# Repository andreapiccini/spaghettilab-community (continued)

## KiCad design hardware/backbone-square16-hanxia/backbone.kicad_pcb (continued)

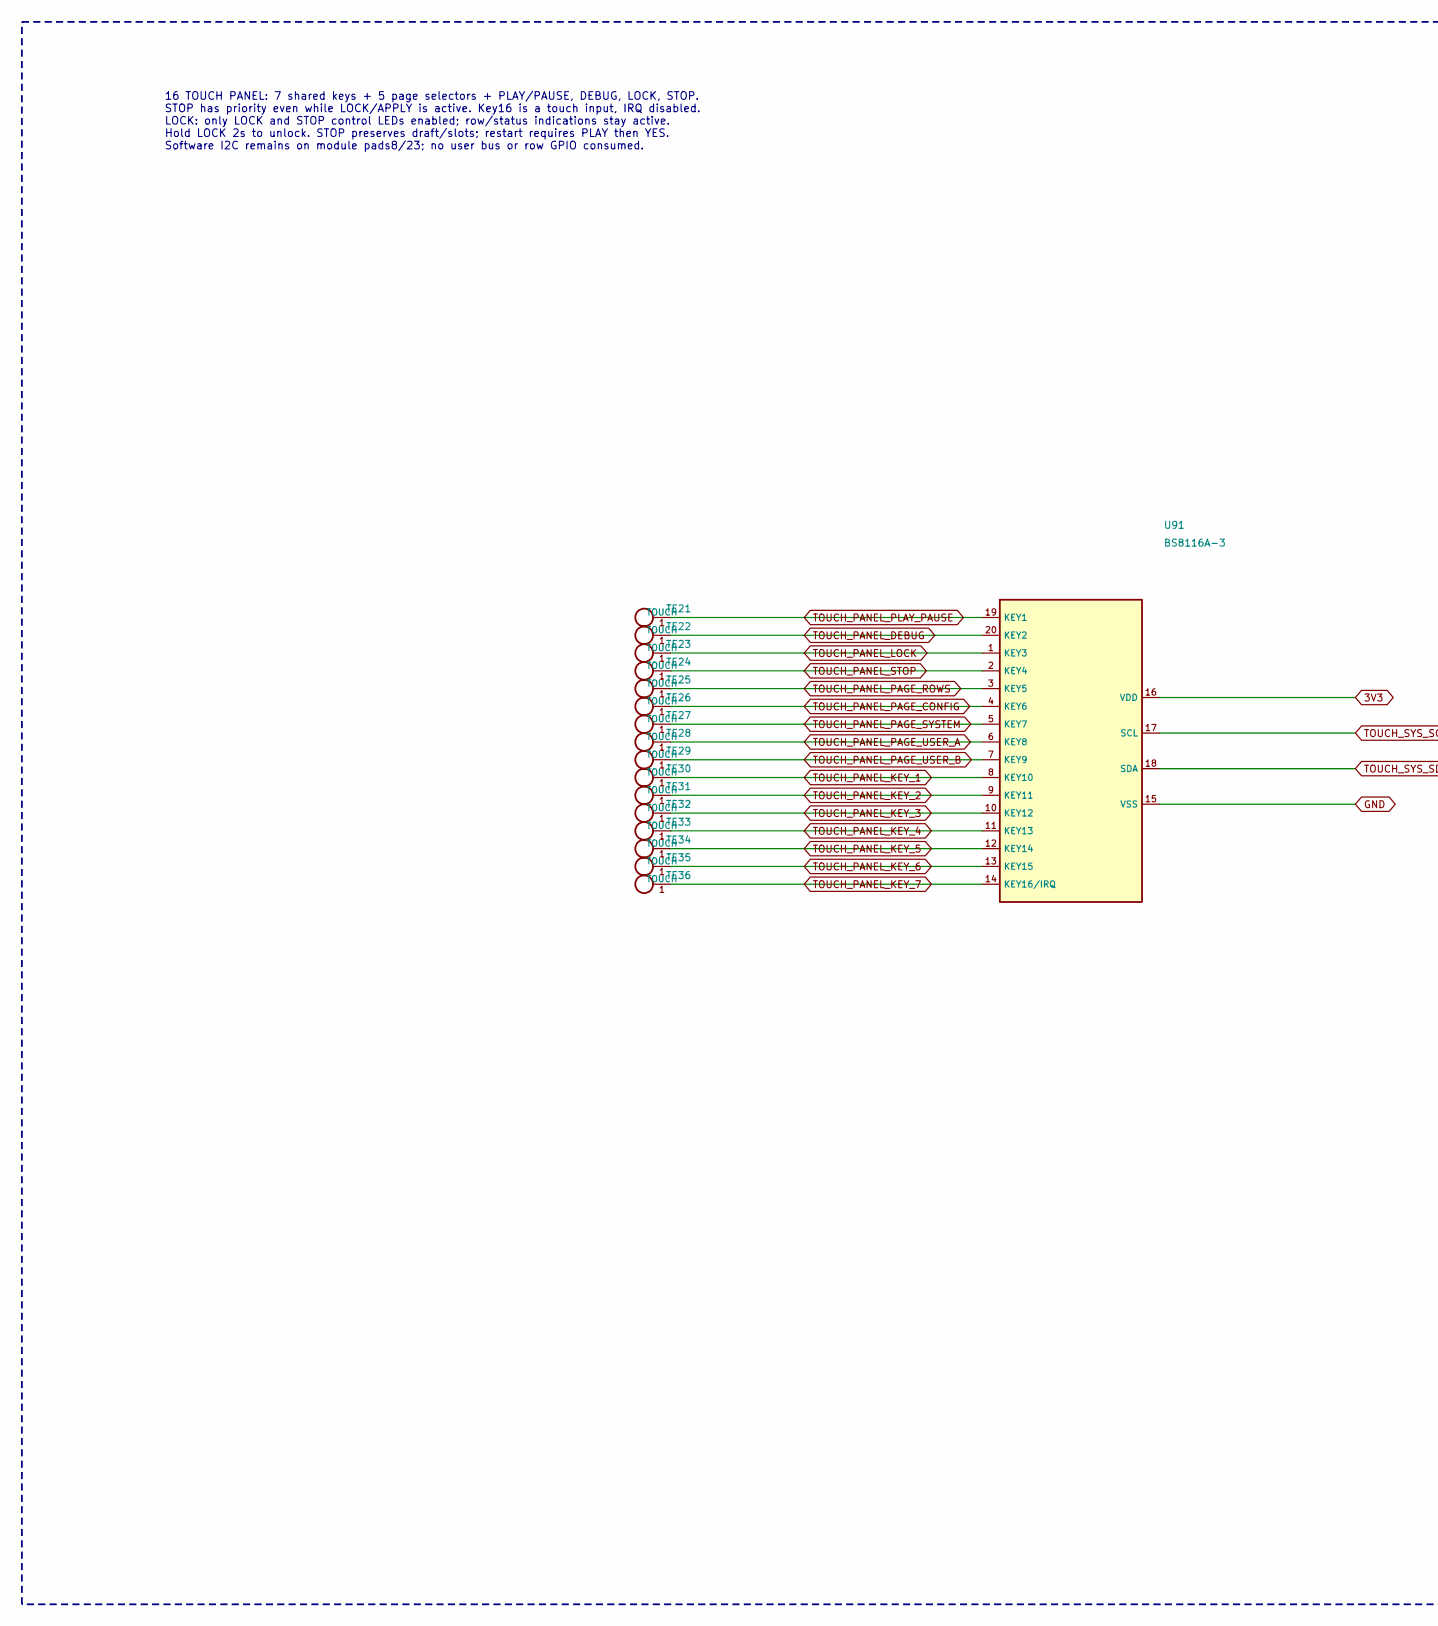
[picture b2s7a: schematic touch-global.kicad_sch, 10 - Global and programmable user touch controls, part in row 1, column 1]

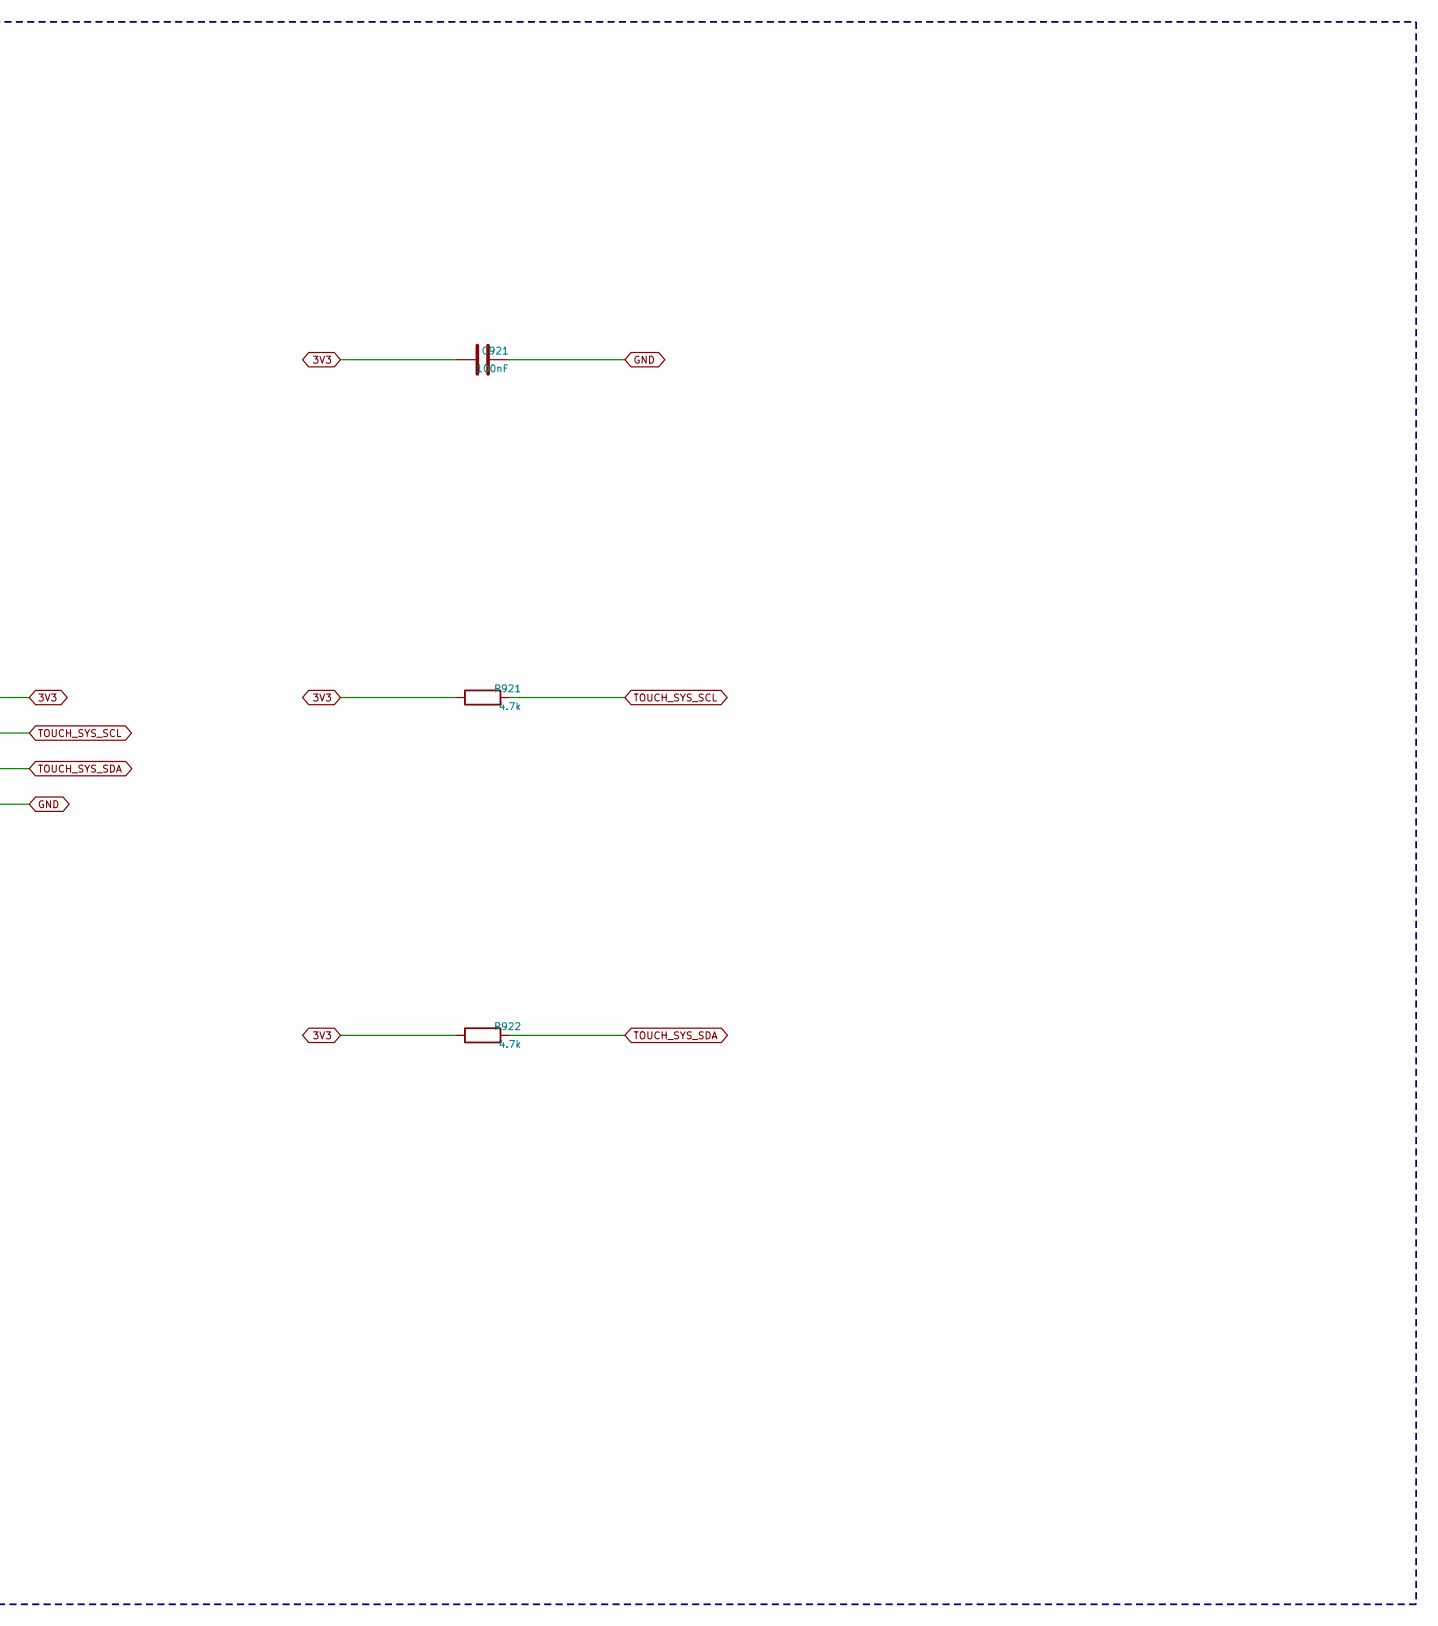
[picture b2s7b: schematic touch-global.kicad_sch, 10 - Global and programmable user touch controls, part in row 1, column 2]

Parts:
C921: 100nF; C_0603_1608Metric
R921, R922: 4.7k; R_0603_1608Metric; MPN 0603WAF4701T5E; LCSC Part C23162
TE21: PLAY_PAUSE; PanelTouch_PLAY_PAUSE
TE22: DEBUG; PanelTouch_DEBUG
TE23: LOCK; PanelTouch_LOCK
TE24: STOP; PanelTouch_STOP
TE25: PAGE_ROWS; PanelTouch_PAGE_ROWS
TE26: PAGE_CONFIG; PanelTouch_PAGE_CONFIG
TE27: PAGE_SYSTEM; PanelTouch_PAGE_SYSTEM
TE28: PAGE_USER_A; PanelTouch_PAGE_USER_A
TE29: PAGE_USER_B; PanelTouch_PAGE_USER_B
TE30: KEY_1; PanelTouch_KEY_1
TE31: KEY_2; PanelTouch_KEY_2
TE32: KEY_3; PanelTouch_KEY_3
TE33: KEY_4; PanelTouch_KEY_4
TE34: KEY_5; PanelTouch_KEY_5
TE35: KEY_6; PanelTouch_KEY_6
TE36: KEY_7; PanelTouch_KEY_7
U91: BS8116A-3; SSOP-20_3.9x8.7mm_P0.635mm

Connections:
3V3: C921.1, R921.1, R922.1, U91.16 (VDD); also elsewhere on the board
GND: C921.2, U91.15 (VSS); also elsewhere on the board
TOUCH_PANEL_DEBUG: TE22.1, U91.20 (KEY2)
TOUCH_PANEL_KEY_1: TE30.1, U91.8 (KEY10)
TOUCH_PANEL_KEY_2: TE31.1, U91.9 (KEY11)
TOUCH_PANEL_KEY_3: TE32.1, U91.10 (KEY12)
TOUCH_PANEL_KEY_4: TE33.1, U91.11 (KEY13)
TOUCH_PANEL_KEY_5: TE34.1, U91.12 (KEY14)
TOUCH_PANEL_KEY_6: TE35.1, U91.13 (KEY15)
TOUCH_PANEL_KEY_7: TE36.1, U91.14 (KEY16/IRQ)
TOUCH_PANEL_LOCK: TE23.1, U91.1 (KEY3)
TOUCH_PANEL_PAGE_CONFIG: TE26.1, U91.4 (KEY6)
TOUCH_PANEL_PAGE_ROWS: TE25.1, U91.3 (KEY5)
TOUCH_PANEL_PAGE_SYSTEM: TE27.1, U91.5 (KEY7)
TOUCH_PANEL_PAGE_USER_A: TE28.1, U91.6 (KEY8)
TOUCH_PANEL_PAGE_USER_B: TE29.1, U91.7 (KEY9)
TOUCH_PANEL_PLAY_PAUSE: TE21.1, U91.19 (KEY1)
TOUCH_PANEL_STOP: TE24.1, U91.2 (KEY4)
TOUCH_SYS_SCL: R921.2, U91.17 (SCL); also elsewhere on the board
TOUCH_SYS_SDA: R922.2, U91.18 (SDA); also elsewhere on the board

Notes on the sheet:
16 TOUCH PANEL: 7 shared keys + 5 page selectors + PLAY/PAUSE, DEBUG, LOCK, STOP. STOP has priority even while LOCK/APPLY is active. Key16 is a touch input, IRQ disabled. LOCK: only LOCK and STOP control LEDs enabled; row/status indications stay active. Hold LOCK 2s to unlock. STOP preserves draft/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

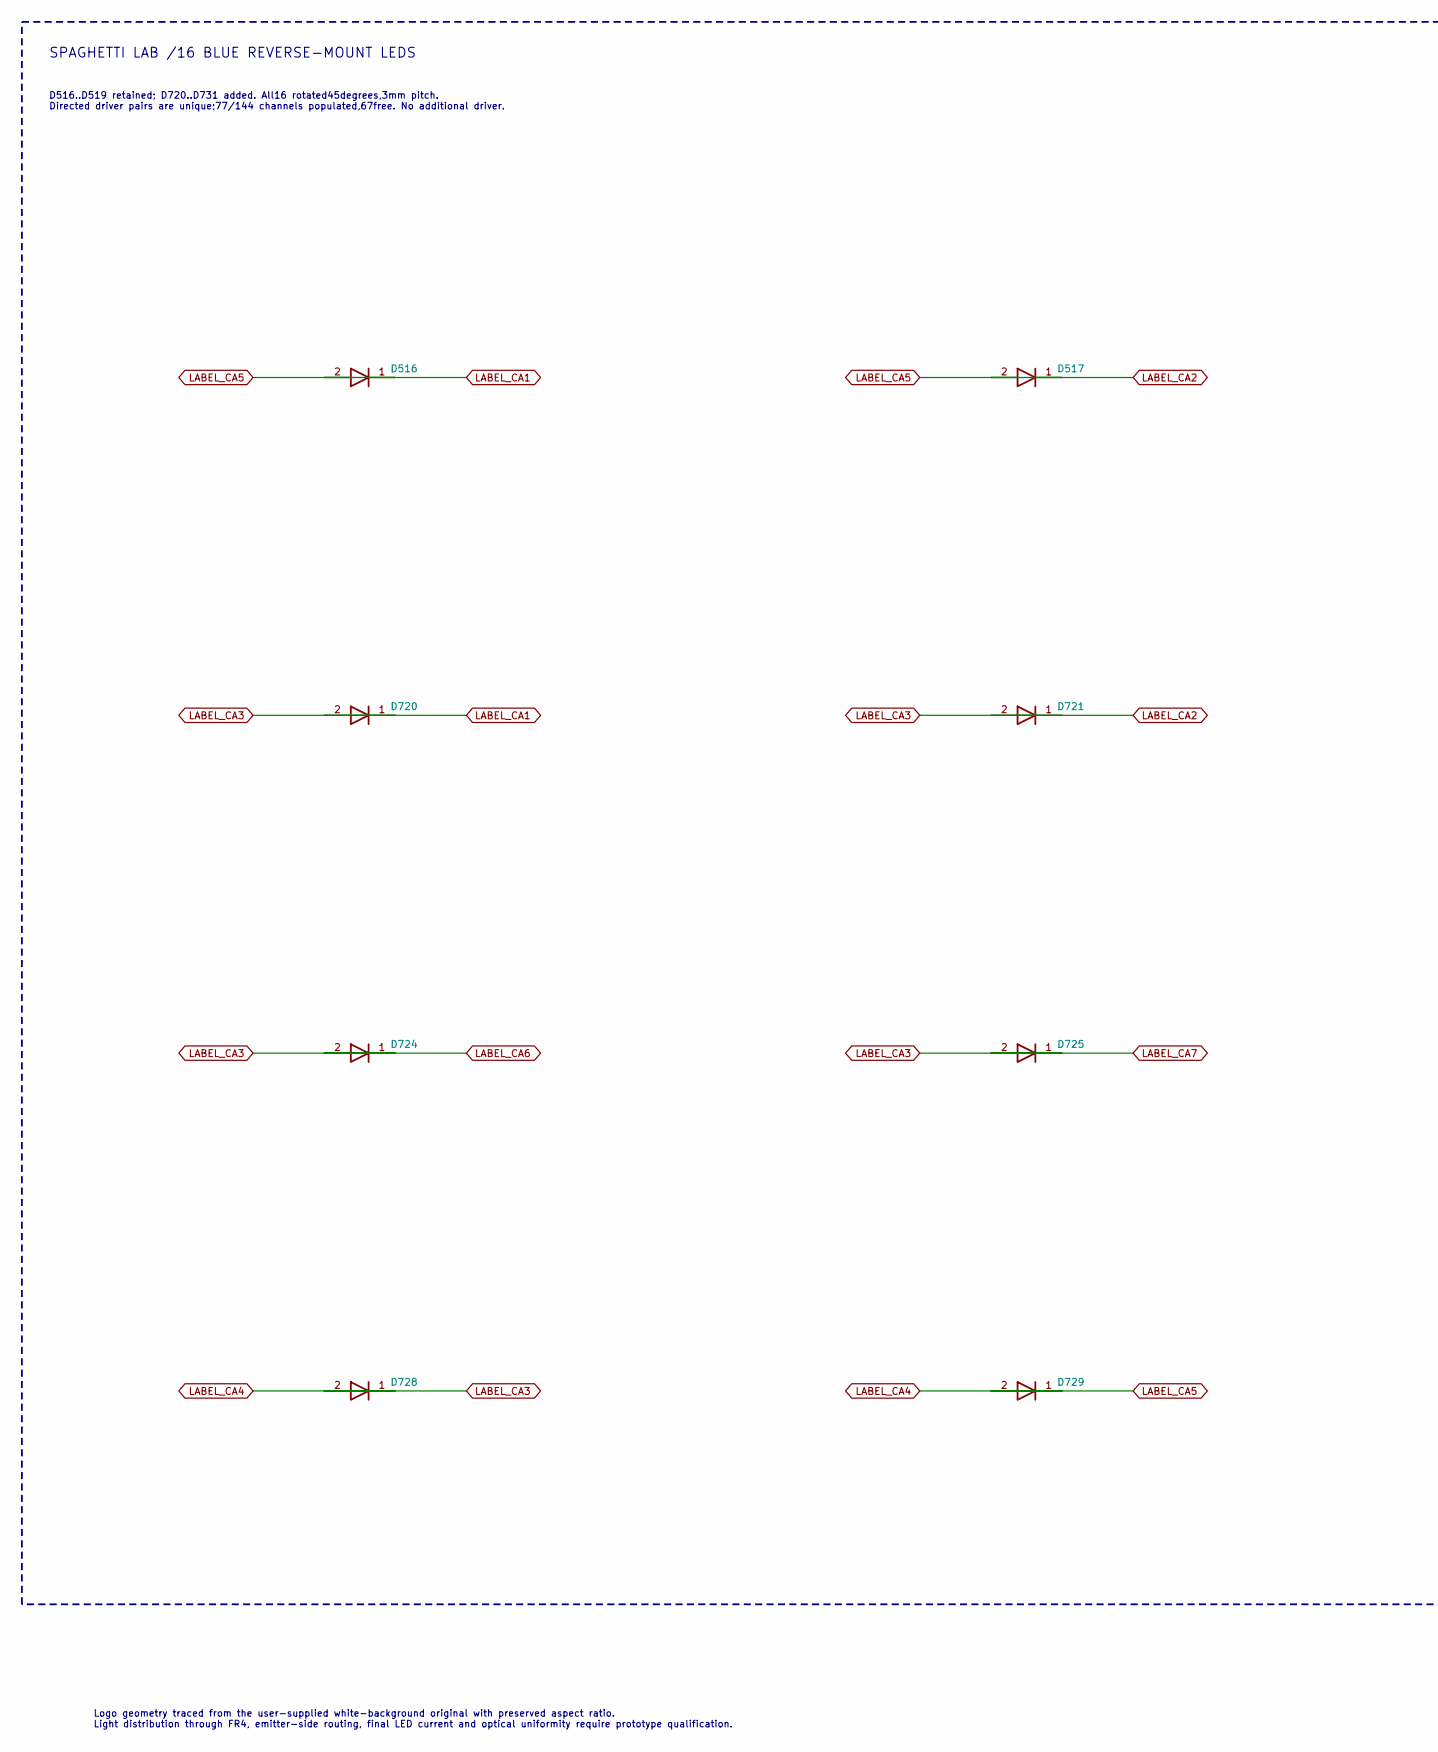
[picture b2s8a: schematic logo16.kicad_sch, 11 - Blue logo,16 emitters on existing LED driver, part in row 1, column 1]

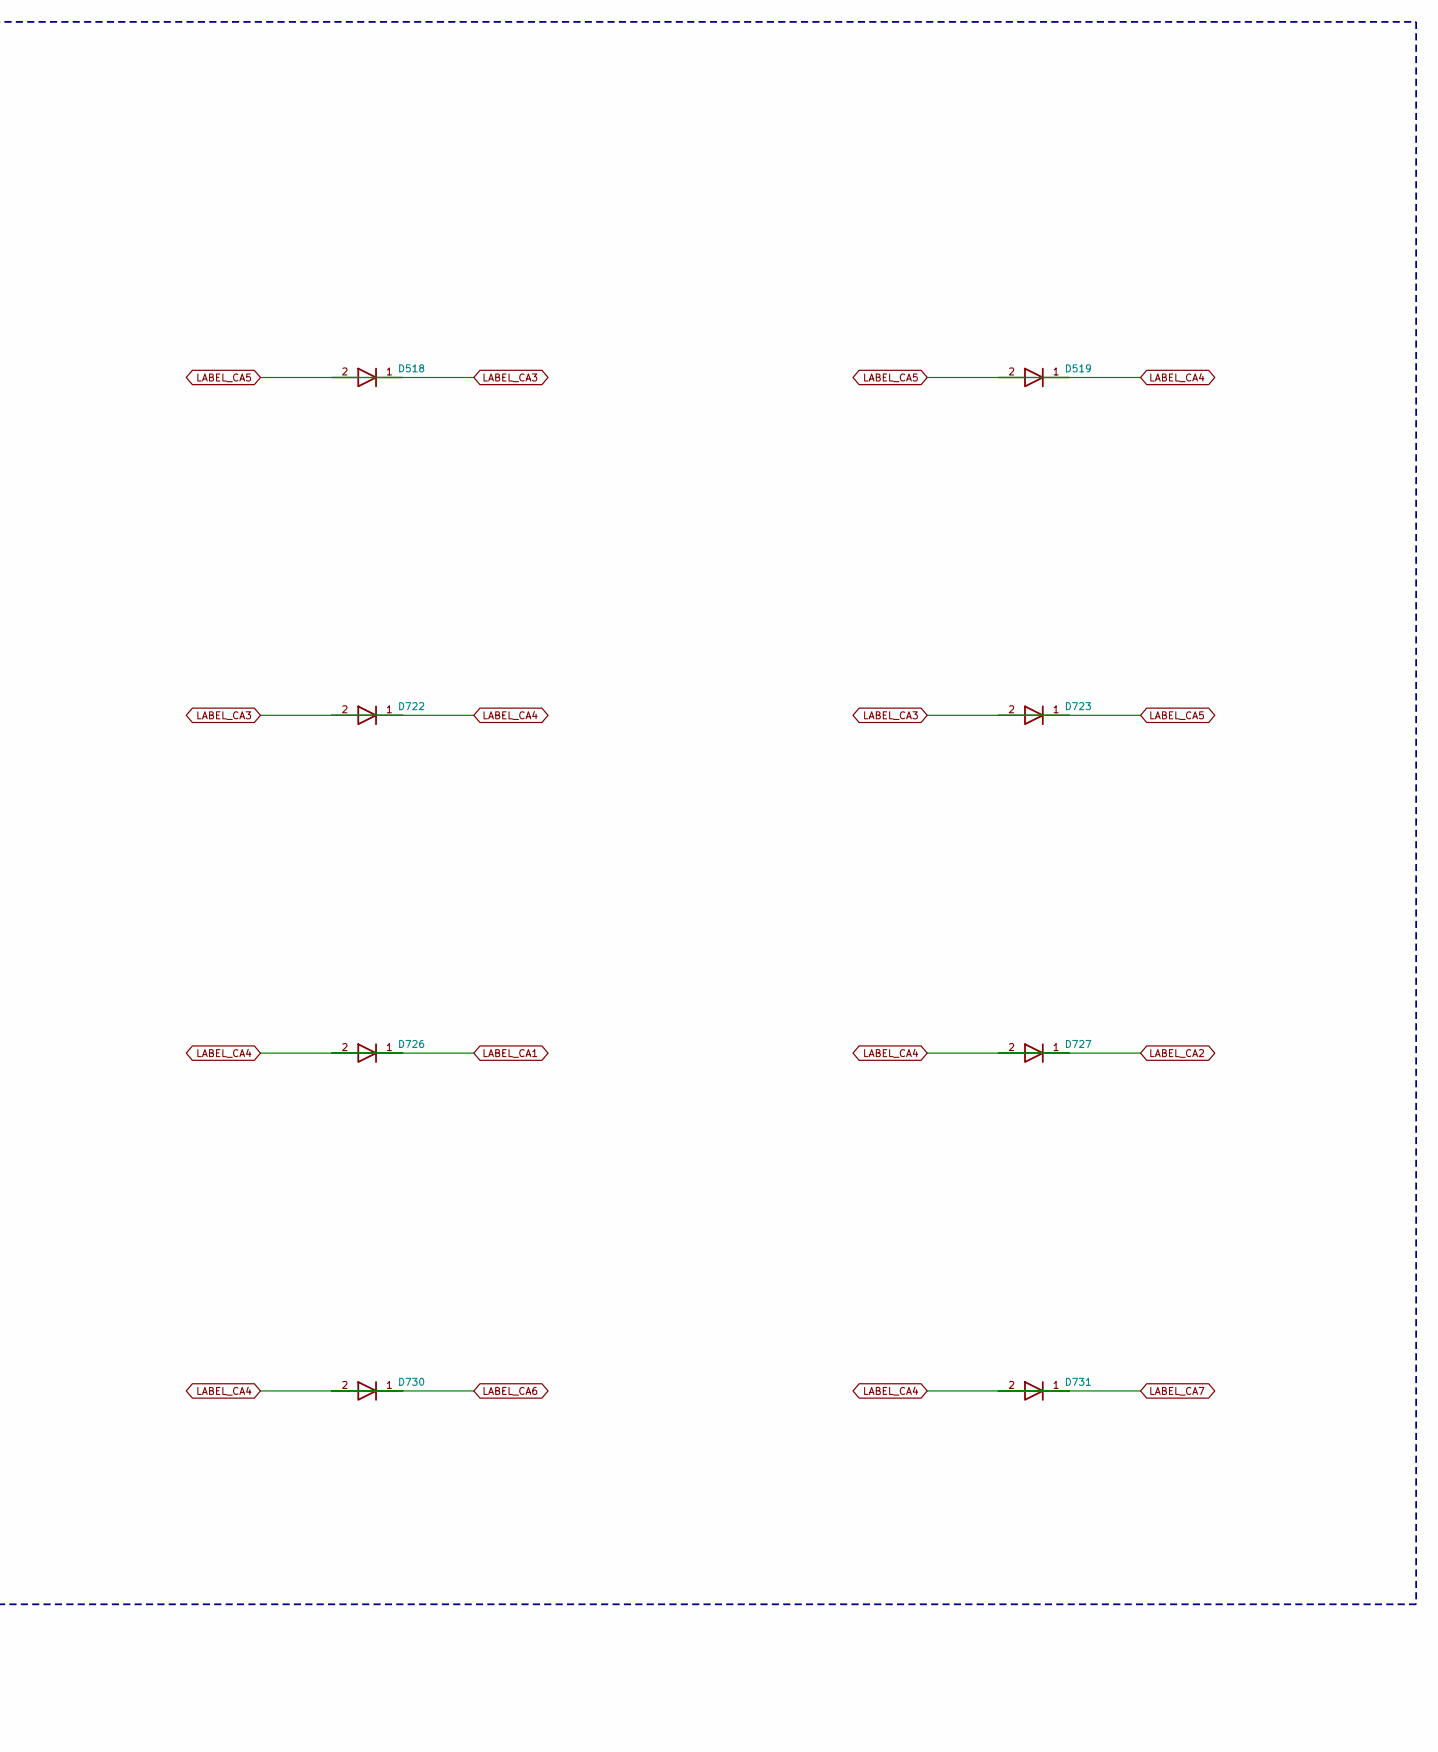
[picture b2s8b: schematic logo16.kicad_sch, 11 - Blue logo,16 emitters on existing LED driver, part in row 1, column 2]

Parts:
D516, D517, D518, D519, D720, D721, D722, D723, D724, D725, D726, D727, D728, D729, D730, D731: XL-3216UBC-FB; XINGLIGHT_XL3216_Reverse_Word_Window; MPN XL-3216UBC-FB; LCSC Part C3646941

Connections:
LABEL_CA1: D516.2 (A), D720.2 (A), D726.2 (A); also elsewhere on the board
LABEL_CA2: D517.2 (A), D721.2 (A), D727.2 (A); also elsewhere on the board
LABEL_CA3: D518.2 (A), D720.1 (K), D721.1 (K), D722.1 (K), D723.1 (K), D724.1 (K), D725.1 (K), D728.2 (A); also elsewhere on the board
LABEL_CA4: D519.2 (A), D722.2 (A), D726.1 (K), D727.1 (K), D728.1 (K), D729.1 (K), D730.1 (K), D731.1 (K); also elsewhere on the board
LABEL_CA5: D516.1 (K), D517.1 (K), D518.1 (K), D519.1 (K), D723.2 (A), D729.2 (A); also elsewhere on the board
LABEL_CA6: D724.2 (A), D730.2 (A); also elsewhere on the board
LABEL_CA7: D725.2 (A), D731.2 (A); also elsewhere on the board

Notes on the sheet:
SPAGHETTI LAB /16 BLUE REVERSE-MOUNT LEDS
D516..D519 retained; D720..D731 added. All16 rotated45degrees,3mm pitch. Directed driver pairs are unique;77/144 channels populated,67free. No additional driver.
Logo geometry traced from the user-supplied white-background original with preserved aspect ratio. Light distribution through FR4, emitter-side routing, final LED current and optical uniformity require prototype qualification.

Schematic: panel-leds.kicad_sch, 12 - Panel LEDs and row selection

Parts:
D800, D801, D802, D803, D804, D805, D806, D807, D808, D809, D810, D811, D812, D813, D814, D815, D816, D817, D818, D819, D820, D821, D822, D823, D824, D825, D826, D827, D828, D829, D830, D831, D832, D833, D834, D835, D836, D837, D838, D839, D840, D841, D842, D843, D844, D845, D846, D847, D848, D849, D850, D851: XL-3216UGC-FB; XINGLIGHT_XL3216_Reverse_Word_Window; LCSC Part C3646937

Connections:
LABEL_CA1: D805.2 (A), D814.2 (A), D822.2 (A); also elsewhere on the board
LABEL_CA2: D806.2 (A), D815.2 (A), D823.2 (A); also elsewhere on the board
LABEL_CA3: D807.2 (A), D811.2 (A), D816.2 (A), D824.2 (A); also elsewhere on the board
LABEL_CA4: D800.1 (K), D801.1 (K), D808.2 (A), D817.2 (A), D825.2 (A); also elsewhere on the board
LABEL_CA5: D802.1 (K), D803.1 (K), D804.1 (K), D809.2 (A), D818.2 (A), D826.2 (A); also elsewhere on the board
LABEL_CA6: D802.2 (A), D805.1 (K), D806.1 (K), D807.1 (K), D808.1 (K), D809.1 (K), D810.1 (K), D819.2 (A), D827.2 (A); also elsewhere on the board
LABEL_CA7: D803.2 (A), D810.2 (A), D811.1 (K), D812.1 (K), D813.1 (K), D820.2 (A), D828.2 (A); also elsewhere on the board
LABEL_CA8: D800.2 (A), D812.2 (A), D814.1 (K), D815.1 (K), D816.1 (K), D817.1 (K), D818.1 (K), D819.1 (K), D820.1 (K), D821.1 (K), D829.2 (A); also elsewhere on the board
LABEL_CA9: D801.2 (A), D804.2 (A), D813.2 (A), D821.2 (A), D822.1 (K), D823.1 (K), D824.1 (K), D825.1 (K), D826.1 (K), D827.1 (K), D828.1 (K), D829.1 (K); also elsewhere on the board
LABEL_CB1: D830.2 (A), D837.2 (A), D845.2 (A); also elsewhere on the board
LABEL_CB2: D831.2 (A), D838.2 (A), D846.2 (A); also elsewhere on the board
LABEL_CB3: D832.2 (A), D839.2 (A), D847.2 (A); also elsewhere on the board
LABEL_CB4: D840.2 (A), D848.2 (A); also elsewhere on the board
LABEL_CB5: D830.1 (K), D831.1 (K), D832.1 (K), D833.1 (K), D834.1 (K), D835.1 (K), D836.1 (K), D841.2 (A), D849.2 (A); also elsewhere on the board
LABEL_CB6: D833.2 (A), D837.1 (K), D838.1 (K), D839.1 (K), D840.1 (K), D841.1 (K), D842.1 (K), D843.1 (K), D844.1 (K), D850.2 (A); also elsewhere on the board
LABEL_CB7: D834.2 (A), D842.2 (A), D845.1 (K), D846.1 (K), D847.1 (K), D848.1 (K), D849.1 (K), D850.1 (K), D851.1 (K); also elsewhere on the board
LABEL_CB8: D835.2 (A), D843.2 (A), D851.2 (A); also elsewhere on the board
LABEL_CB9: D836.2 (A), D844.2 (A); also elsewhere on the board

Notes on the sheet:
Independent PWM channels. LOCK masks all control LEDs except LOCK and STOP. Row selection/status remains visible. Optical windows require translucent overlay/light isolation.
KEY1_PAGE0
KEY1_PAGE1
KEY1_PAGE2
KEY1_PAGE3
KEY1_PAGE4
KEY2_PAGE0
KEY2_PAGE1
KEY2_PAGE2
KEY2_PAGE3
KEY2_PAGE4
KEY3_PAGE0
KEY3_PAGE1
KEY3_PAGE2
KEY3_PAGE3
KEY3_PAGE4
KEY4_PAGE0
KEY4_PAGE1
KEY4_PAGE2
KEY4_PAGE3
KEY4_PAGE4
KEY5_PAGE0
KEY5_PAGE1
KEY5_PAGE2
KEY5_PAGE3
KEY5_PAGE4
KEY6_PAGE0
KEY6_PAGE1
KEY6_PAGE2
KEY6_PAGE3
KEY6_PAGE4
KEY7_PAGE0
KEY7_PAGE1
KEY7_PAGE2
KEY7_PAGE3
KEY7_PAGE4
SELECT_A1
SELECT_A2
SELECT_A3
SELECT_A4

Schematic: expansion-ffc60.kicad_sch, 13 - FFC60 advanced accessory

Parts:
J32: FPC-05FB-60PH20; XUNPU_FPC-05FB-60PH20; LCSC Part C2856839

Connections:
3V3: J32.57; also elsewhere on the board
5V: J32.59, J32.60; also elsewhere on the board
EXP_RESET_N: J32.58; also elsewhere on the board
GND: J32.3, J32.6, J32.9, J32.12, J32.15, J32.18, J32.21, J32.24, J32.27, J32.30, J32.33, J32.36, J32.39, J32.42, J32.45, J32.48, J32.55, J32.56; also elsewhere on the board
GPIO1: J32.2; also elsewhere on the board
GPIO2: J32.26; also elsewhere on the board
GPIO3: J32.5; also elsewhere on the board
GPIO4: J32.14; also elsewhere on the board
GPIO6: J32.8; also elsewhere on the board
GPIO7: J32.11; also elsewhere on the board
GPIO8: J32.29; also elsewhere on the board
GPIO9: J32.32; also elsewhere on the board
GPIO10: J32.35; also elsewhere on the board
GPIO35: J32.17; also elsewhere on the board
GPIO36: J32.20; also elsewhere on the board
GPIO37: J32.23; also elsewhere on the board
GPIO38: J32.38; also elsewhere on the board
GPIO39: J32.41; also elsewhere on the board
GPIO40: J32.44; also elsewhere on the board
GPIO41: J32.47; also elsewhere on the board
GPIO43: J32.52; also elsewhere on the board
GPIO44: J32.51; also elsewhere on the board
I2C_USER_SCL: J32.54; also elsewhere on the board
I2C_USER_SDA: J32.53; also elsewhere on the board
ROW_L01: J32.1; also elsewhere on the board
ROW_L02: J32.4; also elsewhere on the board
ROW_L03: J32.7; also elsewhere on the board
ROW_L04: J32.10; also elsewhere on the board
ROW_L05: J32.13; also elsewhere on the board
ROW_L06: J32.16; also elsewhere on the board
ROW_L07: J32.19; also elsewhere on the board
ROW_L08: J32.22; also elsewhere on the board
ROW_R01: J32.25; also elsewhere on the board
ROW_R02: J32.28; also elsewhere on the board
ROW_R03: J32.31; also elsewhere on the board
ROW_R04: J32.34; also elsewhere on the board
ROW_R05: J32.37; also elsewhere on the board
ROW_R06: J32.40; also elsewhere on the board
ROW_R07: J32.43; also elsewhere on the board
ROW_R08: J32.46; also elsewhere on the board

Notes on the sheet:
FFC60 ADVANCED ACCESSORY - component side, cable through rounded slot 1..48: ROW / GPIO / GND triplets. Do not bridge ROW to GPIO on an accessory. 49..52: auxiliary GPIO aliases (UART0 may emit boot logs); 53/54: user I2C. 55/56 GND; 57 3V3; 58 EXP_RESET_N (LOW = outputs must be disabled); 59/60 5V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

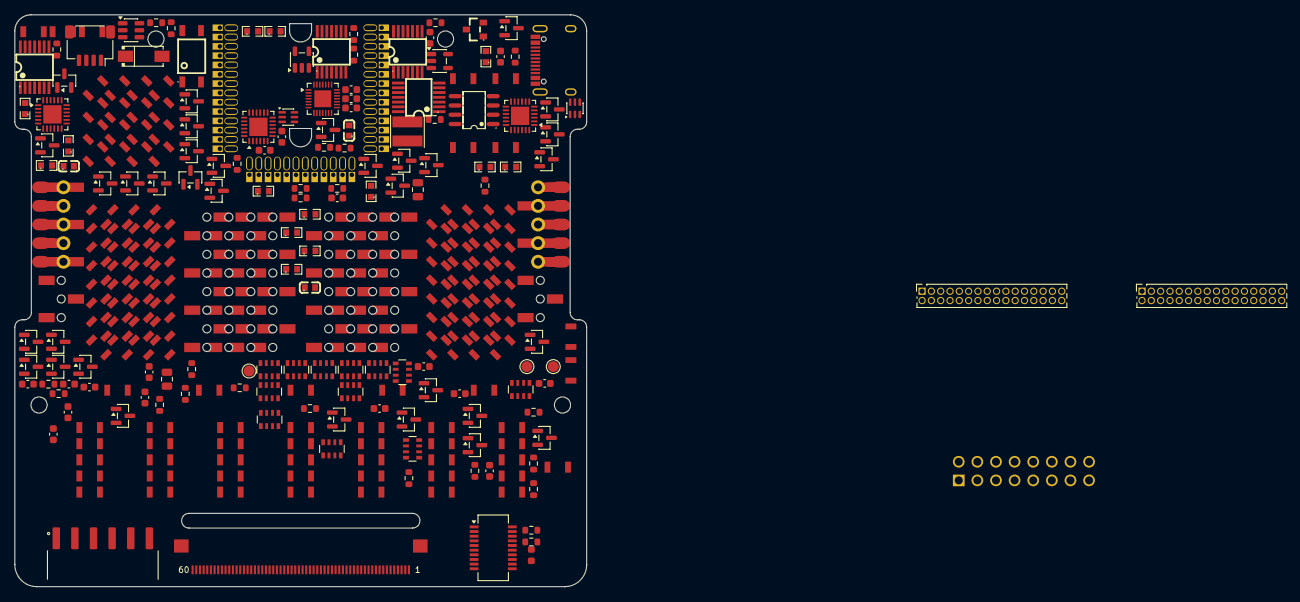
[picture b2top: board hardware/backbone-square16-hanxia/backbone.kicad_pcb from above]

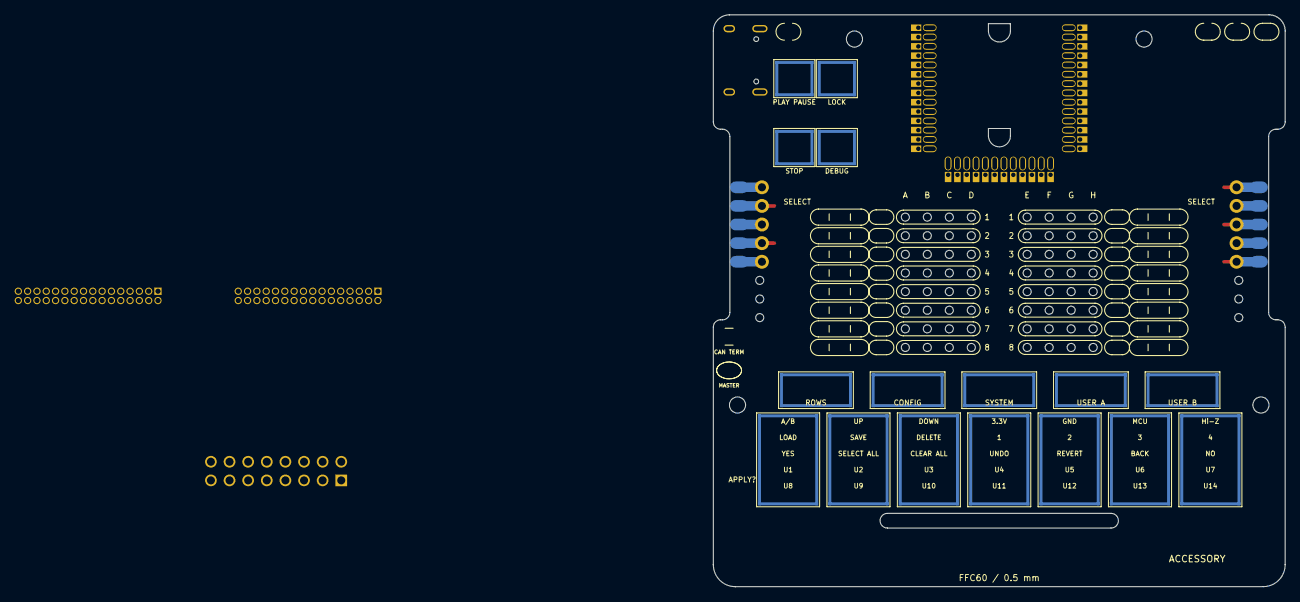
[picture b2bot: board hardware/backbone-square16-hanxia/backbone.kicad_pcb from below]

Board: 4 copper layers, 78.0 x 78.0 mm, 306 parts (17 on the bottom side), 167 nets.

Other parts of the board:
H1, H2, H3, H4: MountingHole; MountingHole_2.2mm_M2_DIN965

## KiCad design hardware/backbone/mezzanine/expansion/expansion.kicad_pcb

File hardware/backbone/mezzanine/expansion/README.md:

# Expansion

Removable AG32 instrumentation module for the SpaghettiLAB backbone.

Open `expansion.kicad_pro`, `expansion.kicad_sch` or `expansion.kicad_pcb`. Carrier: `../../backbone.kicad_pcb`.

PCB components are placed; routing and physical qualification remain open. See [layout and limits](../../MEZZANINE-LAYOUT.md) and [current electrical interface](../../CURRENT-REVISION.md).

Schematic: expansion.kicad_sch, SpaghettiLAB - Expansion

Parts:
C90, C91, C92, C93, C94, C95, C96, C97, C98, C100, C101, C121, C122, C123, C131: 100nF; C_0603_1608Metric; LCSC C14663
C99: 1uF; C_0603_1608Metric; LCSC C15849
J5: FH12-24S-0.5SH(55); Hirose_FH12-24S-0.5SH_1x24-1MP_P0.50mm_Horizontal; LCSC C202112
J10, J11: 61083-061402LF; CONN-SMD_61083-061402LF; LCSC C464610
J12: ESP_AUX_24; PinHeader_2x12_P2.54mm_Vertical_SMD
R70, R72, R73, R79, R80, R83, R84, R109: 10k; R_0603_1608Metric; LCSC C25804
R71, R74, R75, R76, R78, R110, R111: 100k; R_0603_1608Metric; LCSC C25803
R77: 4.7k 0.1% 25ppm; R_0603_1608Metric; LCSC C513565
R81, R82: 22R; R_0603_1608Metric; LCSC C23345
R85, R86, R87, R88: 1k; R_0603_1608Metric; LCSC C21190
R107: 10k; R_0603_1608Metric; MPN 0603WAF1002T5E; LCSC C25804
R108: 100k; R_0603_1608Metric; MPN 0603WAF1003T5E; LCSC C25803
R116: 0R; R_0603_1608Metric; LCSC C21189
TP18, TP19, TP21: SMD/0.6mm; TestPoint_Pad_D1.0mm
TP22: AG_NRST; TestPoint_Pad_D1.0mm
TP23: AG_JTMS; TestPoint_Pad_D1.0mm
TP24: AG_JTCK; TestPoint_Pad_D1.0mm
TP25: AG_JTDI; TestPoint_Pad_D1.0mm
TP26: AG_JTDO; TestPoint_Pad_D1.0mm
TP27: AG_JNTRST; TestPoint_Pad_D1.0mm
TP41: DAC1_SPARE; TestPoint_Pad_D1.0mm
TP42: SPARE_IO_17; TestPoint_Pad_D1.0mm
TP43: SPARE_IO_33; TestPoint_Pad_D1.0mm
TP44: SPARE_IO_34; TestPoint_Pad_D1.0mm
TP45: ISO4_CTRL; TestPoint_Pad_D1.0mm
TP46: ISO5_CTRL; TestPoint_Pad_D1.0mm
TP47: AG_UART_RX; TestPoint_Pad_D1.0mm
TP48: AG_UART_TX; TestPoint_Pad_D1.0mm
TP49: AG_BOOT0; TestPoint_Pad_D1.0mm
U14: AG32VF407VGT6; LQFP-100_L14.0-W14.0-P0.50-LS16.0-TL; LCSC C5336269
U16: INA226AIDGSR; MSOP-10_L3.0-W3.0-P0.50-LS5.0-BL; LCSC C49851
U17, U18, U19: 74HC4051BQ,115; DHVQFN-16_L3.5-W2.5-P0.50-BL-EP; LCSC C128429
U32: DAC_R77_BYPASS; SOT-363_SC-70-6; LCSC C38663
X1: 20MHz; OSC-SMD_4P-L3.2-W2.5-BL; LCSC C390499

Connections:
5V: J10.1, J10.2, J11.1, J11.2, J12.22
/AG_BOOT0: R83.2, R87.2, TP49.1, U14.94 (BOOT0)
/AG_BOOT1: R84.2, U14.37 (BOOT1)
/AG_JNTRST_N: R73.2, TP27.1 (1_1), U14.90 (JNTRST_N)
/AG_JTCK: TP24.1 (1_1), U14.76 (JTCK)
/AG_JTDI: TP25.1 (1_1), U14.77 (JTDI)
/AG_JTDO: TP26.1 (1_1), U14.89 (JTDO)
/AG_JTMS: TP23.1 (1_1), U14.72 (JTMS)
/AG_NRST_N: C92.1, R72.2, R88.2, TP22.1 (1_1), U14.14 (NRST_N)
/CLK20M: U14.12 (OSC_IN), U14.18 (CLK20M_FPGA), X1.3 (OUT)
/DAC1_SPARE: J5.22, TP41.1 (1_1), U14.30 (DAC1_SPARE)
/DAC_INHIBIT: R71.2, U14.81 (DAC_INHIBIT), U19.6 (E_INHIBIT)
/DAC_S0: U14.78 (DAC_S0), U19.11 (S0)
/DAC_S1: U14.79 (DAC_S1), U19.10 (S1)
/DAC_S2: U14.80 (DAC_S2), U19.9 (S2)
/INA_ALERT_N: R76.2, U14.84 (INA_ALERT_N), U16.3 (Alert)
/SHUNT_HIGH_SELECTED: U16.10 (VIN+), U17.3 (Z)
/SHUNT_LOW_SELECTED: U16.8 (VBUS), U16.9 (VIN-), U18.3 (Z)
/SPARE_IO_17: TP42.1 (1_1), U14.17 (ADC_IN12_SPARE)
/SPARE_IO_33: TP43.1 (1_1), U14.33 (ADC_IN14_SPARE)
/SPARE_IO_34: TP44.1 (1_1), U14.34 (ADC_IN15_SPARE)
/USB_AG_D+: R82.1, U14.71 (USB_DP)
/USB_AG_D-: R81.1, U14.70 (USB_DM)
A0: J10.6, J12.6, U14.38 (ESP_A0)
A1: J10.9, J12.7, U14.39 (ESP_A1)
A2: J10.13, J12.8, U14.40 (ESP_A2)
A3: J10.17, J12.9, U14.41 (ESP_A3)
A4: J10.21, J12.10, U14.42 (ESP_A4)
A5: J10.24, J12.11, U14.43 (ESP_A5)
AG_BOOT_UART_RX: R85.2, TP47.1, U14.69 (ISO5_N)
AG_BOOT_UART_TX: R86.1, TP48.1, U14.68 (ISO4_N)
AG_CAN_TX: J10.34, U14.92 (CAN_TX)
AG_ISO4_N: J10.36, U14.35 (ADC_IN8_SPARE)
AG_ISO5_N: J10.37, U14.36 (ADC_IN9_SPARE)
AG_LED_DATA: J10.38, U14.7 (LED_DATA)
BOOT: J10.28, J12.1, U14.61 (N_GATE4)
CAN_H: J11.46
CAN_L: J11.47
CAN_RX: J5.8, J10.39, U14.93 (CAN_RX)
CTRL13: J10.41, J12.12, R74.2, U14.86 (SPI_CS_N)
CTRL14: J5.19, J10.42, U14.87 (SPI_SCLK)
DAC_BYPASS_N: R78.2, U14.85 (DAC_BYPASS_N), U32.6 (S_AG_READY)
DAC_LIMITED: R77.2, U14.16 (ADC_LIMIT/IN11), U19.3 (Z), U32.4 (A_OUT)
DAC_RAW: R77.1, U14.15 (ADC_RAW/IN10), U14.29 (DAC0_OUT), U32.3 (B1_ESP)
ESP35_AUX: J10.43, J12.13, U14.64 (ISO0_N)
ESP36_AUX: J10.44, J12.14, U14.65 (ISO1_N)
ESP37_AUX: J10.46, J12.15, U14.66 (ISO2_N)
ESP_AG_BOOT0: J10.29, J12.2, R87.1, U14.67 (ISO3_N)
ESP_AG_RESET_N: J10.31, J12.3, R88.1, U14.82 (INA_SDA)
ESP_CAN_TX: J5.7, J10.47, U14.55 (N_GATE1)
ESP_ISO4_N: J5.12, J10.48, U14.56 (P_GATE2_N)
ESP_ISO5_N: J5.13, J10.49, U14.57 (N_GATE2)
ESP_LED_DATA: J5.9, J10.51, U14.58 (P_GATE3_N)
ESP_PROG_RX: J10.32, J12.4, R86.2, U14.83 (INA_SCL)
ESP_PROG_TX: J10.33, J12.5, R85.1, U14.54 (P_GATE1_N)
EXT_SPI_CS_N: J5.4, J10.52, R108.1, U14.60 (P_GATE4_N)
GND: C90.2, C91.2, C92.2, C93.2, C94.2, C95.2, C96.2, C97.2, C98.2, C99.2, C100.2, C101.2, C121.2, C122.2, C123.2, C131.2, J5.1, J5.6, J5.10, J5.14, J5.24, J10.5, J10.10, J10.15, J10.20, J10.25, J10.30, J10.35, J10.40, J10.45, J10.50, J10.55, J10.57, J10.58, J10.59, J10.60, J11.5, J11.10, J11.15, J11.20, J11.25, J11.30, J11.35, J11.40, J11.45, J11.50, J11.55, J11.57, J11.58, J11.59, J11.60, J12.20, J12.23, R83.1, R84.1, R111.2, R116.2, TP21.1 (1_1), U14.10 (VSS33), U14.20 (VSSA), U14.27 (VSS33), U14.74 (VSS33), U14.99 (VSS33), U16.1 (A1), U16.2 (A0), U16.7 (GND), U17.7 (VEE), U17.8 (GND), U18.7 (VEE), U18.8 (GND), U19.7 (VEE), U19.8 (GND), U32.2 (GND), X1.2 (GND)
GPIO6_UPPER: J5.3, J11.12
GPIO12_UPPER: J5.5, J11.13
GPIO39_UPPER: J11.53
GPIO40_UPPER: J11.54
GPIO41_UPPER: J5.15, J11.14
GPIO42_UPPER: J5.16, J11.11
IO3: J10.53, J12.16, R75.2, U14.97 (ESP_IRQ_N)
IO4: J5.17, J10.54, U14.95 (EXT_I2C_SDA), U16.4 (SDA)
IO5: J5.18, J11.7, U14.96 (EXT_I2C_SCL), U16.5 (SCL)
IO45: J10.56, J12.17, U14.62 (P_GATE5_N)
IO46: J11.6, J12.18, U14.63 (N_GATE5)
ISO_A0_N: J11.41
ISO_A1_N: J11.42
ISO_A2_N: J11.43
ISO_A3_N: J11.44
ISO_A4_N: J11.8, TP45.1 (1_1)
ISO_A5_N: J11.9, TP46.1 (1_1)
LED_EXP_DATA: J11.52
MEAS_INHIBIT: R70.2, U14.5 (MEAS_INHIBIT), U17.6 (E_INHIBIT), U18.6 (E_INHIBIT)
MEAS_S0: R79.2, U14.2 (MEAS_S0), U17.11 (S0), U18.11 (S0)
MEAS_S1: R80.2, U14.3 (MEAS_S1), U17.10 (S1), U18.10 (S1)
MEAS_S2: R107.1, U14.4 (MEAS_S2), U17.9 (S2), U18.9 (S2)
MEZZ_OWNER: J11.16, R109.2, U14.52 (P_GATE0_N)
MEZZ_PRESENT_N: J5.11, J11.17, R116.1, U14.59 (N_GATE3)
N_A0: J10.7, U14.44 (DRIVE_A0), U17.13 (Y0), U19.13 (Y0)
N_A1: J10.11, U14.45 (DRIVE_A1), U17.14 (Y1), U19.14 (Y1)
N_A2: J10.14, U14.46 (DRIVE_A2), U17.15 (Y2), U19.15 (Y2)
N_A3: J10.18, U14.47 (DRIVE_A3), U17.12 (Y3), U19.12 (Y3)
N_A4: J10.22, U14.48 (DRIVE_A4), U17.1 (Y4), U19.1 (Y4)
N_A5: J10.26, U14.51 (DRIVE_A5), U17.5 (Y5), U19.5 (Y5)
N_GATE_0: J11.27
N_GATE_1: J11.29
N_GATE_2: J11.32
N_GATE_3: J11.34
N_GATE_4: J11.37
N_GATE_5: J11.39
PORT_A0: J10.8, U14.23 (ADC_A0/IN0), U18.13 (Y0)
PORT_A1: J10.12, U14.24 (ADC_A1/IN1), U18.14 (Y1)
PORT_A2: J10.16, U14.25 (ADC_A2/IN2), U18.15 (Y2)
PORT_A3: J10.19, U14.26 (ADC_A3/IN3), U18.12 (Y3)
PORT_A4: J10.23, U14.31 (ADC_A4/IN6), U18.1 (Y4)
PORT_A5: J10.27, U14.32 (ADC_A5/IN7), U18.5 (Y5)
P_GATE_0: J11.26
P_GATE_1: J11.28
P_GATE_2: J11.31
P_GATE_3: J11.33
P_GATE_4: J11.36
P_GATE_5: J11.38
SPI_MISO: J5.21, J11.18, TP18.1 (1_1), U14.91 (SPI_MISO)
SPI_MOSI: J5.20, J11.19, TP19.1 (1_1), U14.88 (SPI_MOSI)
TERM_CTRL_IN: J11.48
TERM_CTRL_OUT: J11.49
USB_SW_AG_N: J11.21, R81.2
USB_SW_AG_P: J11.22, R82.2
USB_VBUS_SENSE: R110.2, R111.1, U14.53 (N_GATE0)
VBUS: J11.51, R110.1
VCORE: C90.1, C91.1, C93.1, C94.1, C95.1, C96.1, C97.1, C98.1, C99.1, C100.1, C101.1, C121.1, C122.1, C123.1, C131.1, J5.2, J5.23, J10.3, J10.4, J11.3, J11.4, J12.21, R70.1, R71.1, R72.1, R73.1, R74.1, R75.1, R76.1, R78.1, R79.1, R80.1, R107.2, R108.2, R109.1, U14.6 (VBAT), U14.11 (VDD33), U14.21 (VREFP), U14.22 (VDDA), U14.28 (VDD33), U14.50 (VDD33), U14.75 (VDD33), U14.100 (VDD33), U16.6 (VS+), U17.16 (VCC), U17.17 (EP_VCC), U18.16 (VCC), U18.17 (EP_VCC), U19.16 (VCC), U19.17 (EP_VCC), U32.5 (VCC), X1.1 (OE/#ST), X1.4 (VCC)
~RESET: J11.24, J12.19, U14.98 (ESP_RESET_OD)

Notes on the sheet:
U14D + U16-U18 | SHARED CURRENT MONITOR
Selects one experiment row at a time and reads its shunt voltage.
Match both mux channel selections. Inhibit, select, settle, then start a fresh INA226 conversion. I2C is shared; AG32 alone selects the current muxes.
U14E + U19 / U32 | ADJUSTABLE TEST SIGNAL
Applies a small test voltage to one selected experiment row.
Internal ADC/DAC only. Scan with power MOSFETs OFF, other drivers Hi-Z and ESP bypass OPEN. Disable R77 bypass for limited stimulus. A return path is required; occupancy detection is not guaranteed.
U14F + X1 | CLOCK, POWER AND RECOVERY
Starts the AG32 controller and provides local power bypass and debug access.
U14G | SPARE I/O AND ISOLATION CONTROL
Keeps spare controller connections and the last two port-enable signals accessible.
ESP32 TO AG32 | PROGRAMMING AND RECOVERY
Allows loading firmware through ESP32 or an external recovery connection.
ESP TX/RX -> AG UART RX/TX. Boot and reset access are preserved. Recovery requires ESP pins released. Firmware and bootloader sequence are not implemented by this schematic.
J5 / J12 | EXTERNAL EXPANSION
Brings ESP32 and supported AG32 signals to the flat cable and auxiliary header.
GPIO35/36/37 use carrier DNP links. Shared I2C/SPI and boot/strap pins are not unrestricted GPIO. All headers are 3.3 V logic.
J10 / J11 | CARRIER INTERFACE - 2 x 60 CONTACTS
120 contacts: existing services + 22 future-module signals; J11.53/54 carry GPIO39/40; J11.23/56 remain reserved.
U14B | OWNERSHIP AND GPIO OBSERVATION
Manages the module role and observes additional ESP32 signals.
AG52: release or drive LOW in open-drain; do not drive HIGH. OBS inputs stay Hi-Z. FPGA routing and protocol
bridges still require toolchain validation.
U14C | USB, CAN AND CONTROL LINKS
Exchanges messages with the computer, carrier and optional ESP32.
U14A | SIX-PORT OBSERVATION
Observes the experiment while leaving the direct ESP32 path available.
A0-A5 = ESP side; N_A0-A5 = driver side; PORT_A0-A5 = external side after shunt. Inline FPGA
requires carrier bypass switches OPEN and validated HDL.
MODULE PRESENCE AND PRIORITY
Reports the module presence and selects its shared services.
R109 = 10k pull-up claims services on insertion. R116 pulls MEZZ_PRESENT_N LOW. No
automatic detection of a failed or unpowered fitted module.
SPAGHETTILAB | EXPANSION - AG32 INSTRUMENT MODULE
Functional groups | local wires retained | power shown with symbols | cross-block links use named nets
U14A-U14G are units of ONE physical AG32. All measurements and FPGA features require firmware and prototype validation.
Future-module contacts are intentionally unused by this AG32 module. No new AG32 pins are
assigned.

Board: 4 copper layers, 70 parts (33 on the bottom side), 92 nets, no tracks yet.
